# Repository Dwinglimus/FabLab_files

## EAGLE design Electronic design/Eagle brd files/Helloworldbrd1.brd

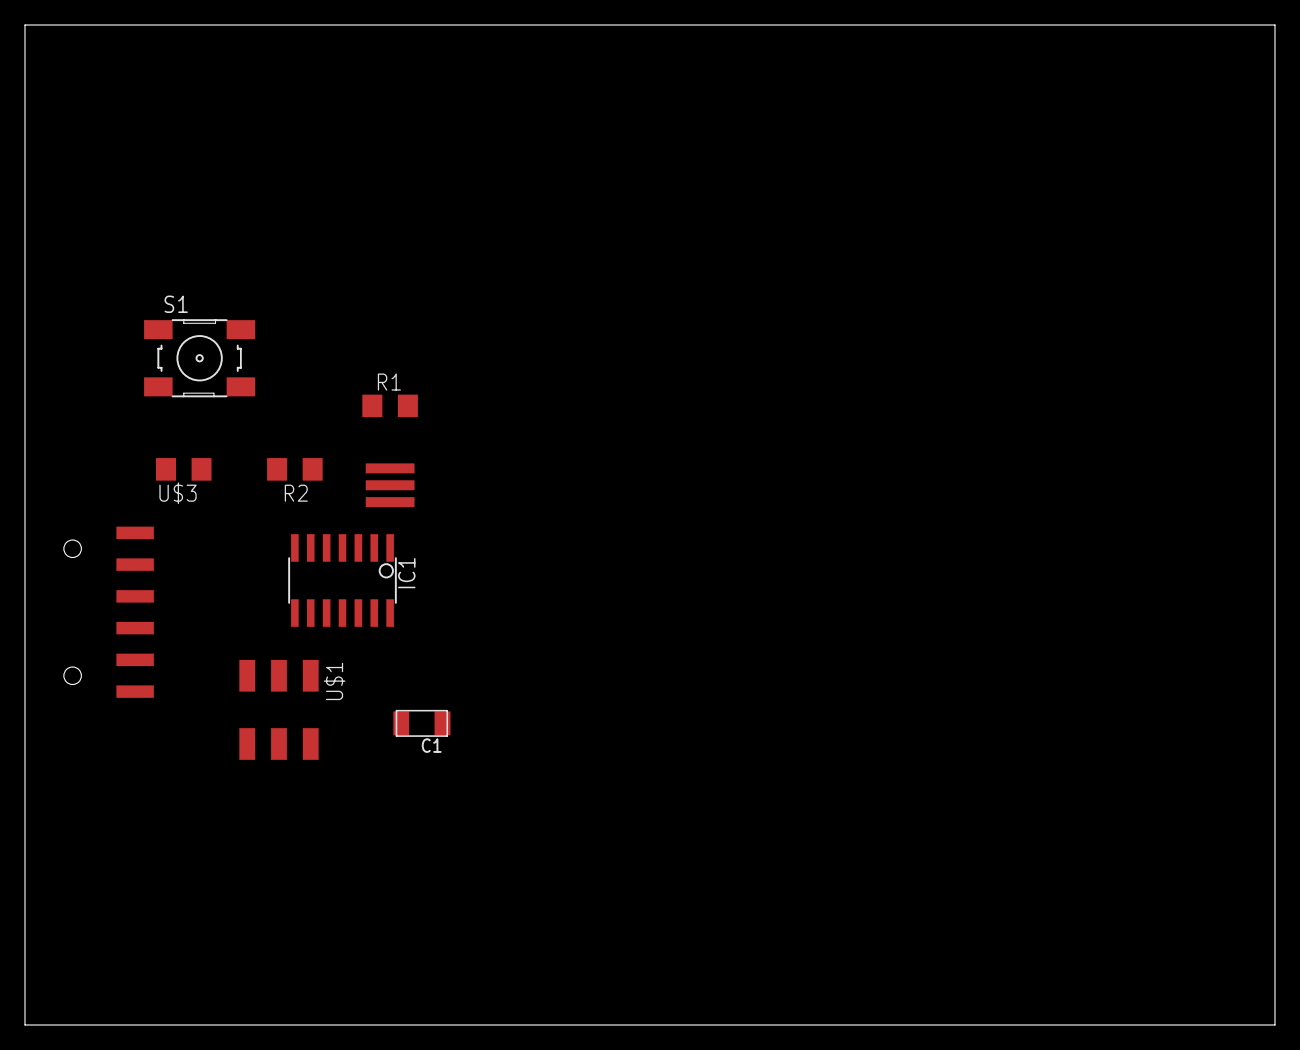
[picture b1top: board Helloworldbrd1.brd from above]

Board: 2 copper layers, 100.0 x 80.0 mm, 9 parts (0 on the bottom side), 13 nets, no tracks yet.

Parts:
C1: 1UF; C1206FAB
IC1: ATTINY44-SSU; SOIC14
JP1: 1X06-SMD
R1: 10k; R1206
R2: 499; R1206
S1: 6MM_SWITCH
U$1: AVRISPSMD; 2X03SMD
U$2: RESONATOR; EFOBM
U$3: LED; LED1206

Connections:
BUTTON: IC1.10, S1.1, S1.2
GND: C1.2, IC1.14, JP1.6, S1.3, S1.4, U$1.6, U$2.2, U$3.2
LED: IC1.6, R2.2
MISO: IC1.8, U$1.1
MOSI: IC1.7, U$1.4
unnamed: IC1.2, U$2.1
unnamed: R2.1, U$3.1
unnamed: IC1.3, U$2.3
RST: IC1.4, R1.1, U$1.5
RX: IC1.12, JP1.2
SCK: IC1.9, U$1.3
TX: IC1.13, JP1.3
VCC: C1.1, IC1.1, JP1.4, R1.2, U$1.2

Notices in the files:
parts and their libraries:
SparkFun: Licensing: CC v3.0 Share-Alike You are welcome to use this library for commercial purposes.
